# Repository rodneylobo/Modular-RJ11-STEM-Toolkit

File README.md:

# Modular-RJ11-STEM-Toolkit
This Toolkit prototype because of MIT's Thrifty MakerSpace project.
The prototype was tested in low income schools with enormous success in inducing the habit of 'Making' in kids.
The Modularity in the design makes the kit more affordable than existing kits.

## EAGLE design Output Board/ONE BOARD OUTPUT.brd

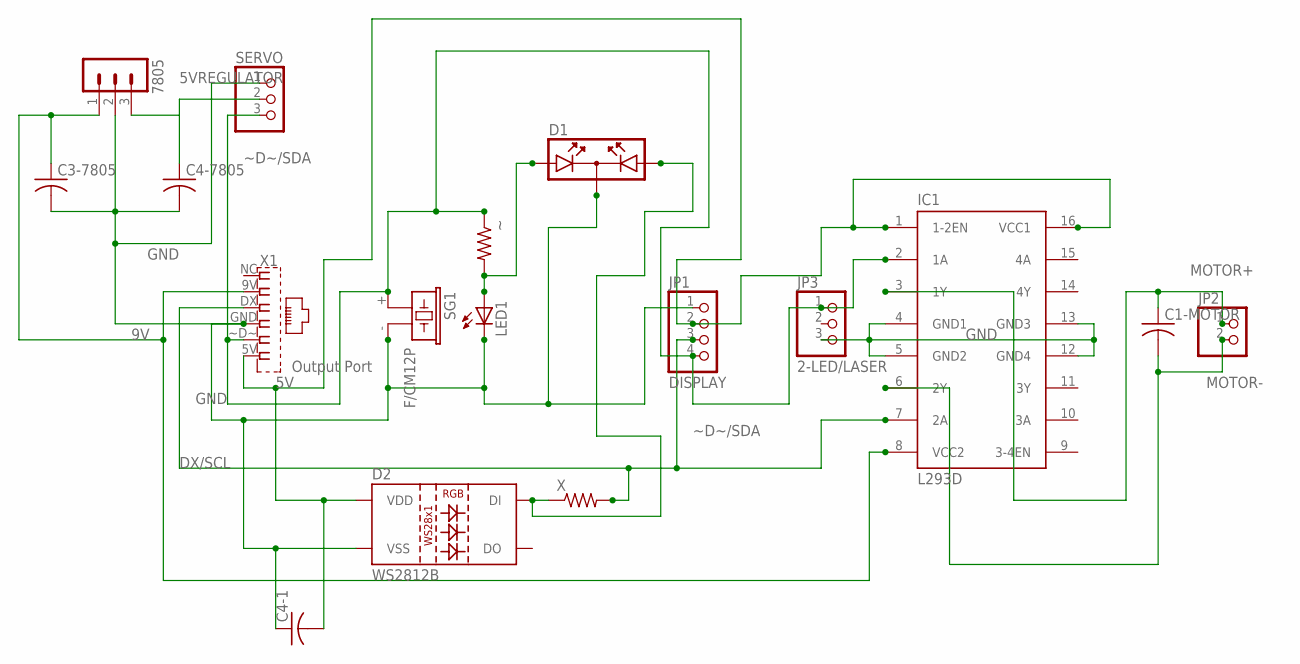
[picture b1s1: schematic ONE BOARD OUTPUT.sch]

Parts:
7805: MA03-1
C1-MOTOR, C3-7805, C4-1, C4-7805: C-US025-030X050; C025-030X050
D1: DUOLED
D2: WS2812B
IC1: L293D; DIL16
JP1: DISPLAY; 1X04
JP2: PINHD-1X2; 1X02
JP3: 2-LED/LASER; 1X03
LED1: LED10MM
SERVO: PINHD-1X3; 1X03
SG1: F/CM12P
X: R-US_0207/10; 0207/10
X1: Output Port; ELEMENTORY-OUT-SEN
~: R-US_0207/10; 0207/10

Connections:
5V: C4-1.2, D2.1 (VDD), IC1.1 (1-2EN), IC1.16 (VCC1), JP1.2, X1.5V (6)
5VREGULATOR: 7805.3, C4-7805.1, SERVO.2
9V: 7805.1, C3-7805.1, IC1.8 (VCC2), X1.9V (2)
DX/SCL: IC1.7 (2A), JP1.3, X.2, X1.DX (3)
GND: 7805.2, C3-7805.2, C4-1.1, C4-7805.2, D1.K, D2.3 (VSS), IC1.4 (GND1), IC1.5 (GND2), IC1.12 (GND4), IC1.13 (GND3), JP1.1, JP3.3, LED1.K (C), SERVO.1, SG1.- (2), X1.GND (4)
LED_SIG: D1.A1, LED1.A, ~.2
MOTOR+: C1-MOTOR.1, IC1.3 (1Y), JP2.1
MOTOR-: C1-MOTOR.2, IC1.6 (2Y), JP2.2
unnamed: D1.A2, D2.4 (DI), X.1
~D~/SDA: IC1.2 (1A), JP1.4, JP3.1, SERVO.3, SG1.+ (1), X1.~D~ (5), ~.1

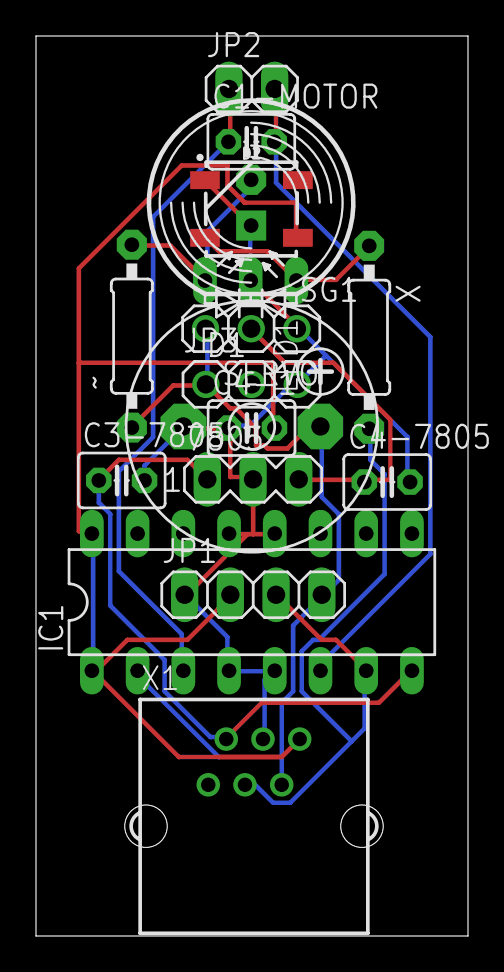
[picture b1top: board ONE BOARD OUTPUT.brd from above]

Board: 2 copper layers, 24.0 x 50.0 mm, 17 parts (0 on the bottom side), 10 nets.

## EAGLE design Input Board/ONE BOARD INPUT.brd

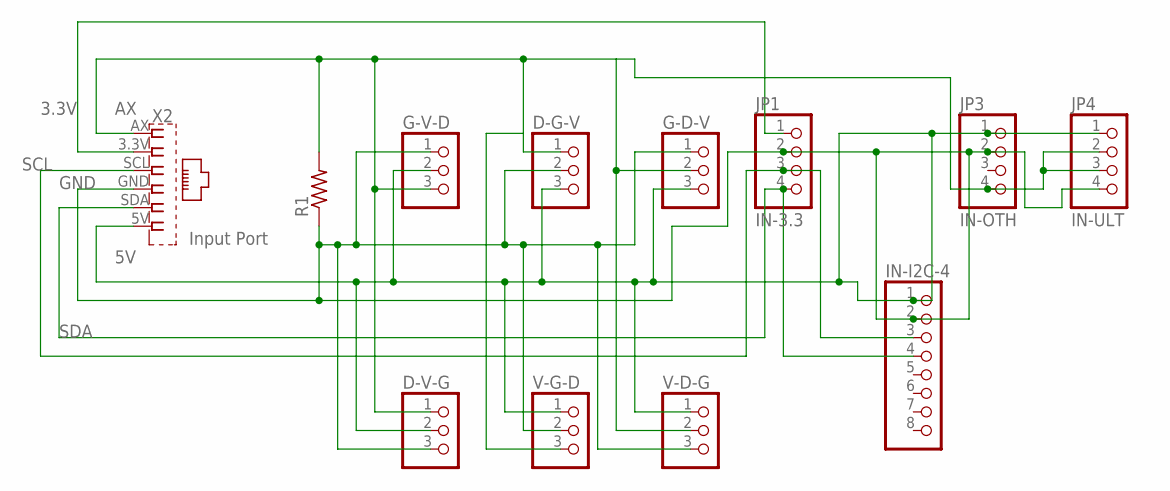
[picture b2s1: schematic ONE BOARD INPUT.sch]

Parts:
D-G-V: PINHD-1X3; 1X03
D-V-G: PINHD-1X3; 1X03
G-D-V: PINHD-1X3; 1X03
G-V-D: PINHD-1X3; 1X03
IN-I2C-4: PINHD-1X8; 1X08
JP1: IN-3.3; 1X04
JP3: IN-OTH; 1X04
JP4: IN-ULT; 1X04
R1: R-US_0207/10; 0207/10
V-D-G: PINHD-1X3; 1X03
V-G-D: PINHD-1X3; 1X03
X2: Input Port; ELEMENTORY-IN-SEN

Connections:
3.3V: JP1.1, X2.3.3V (2)
5V: D-G-V.3, D-V-G.2, G-D-V.3, G-V-D.2, IN-I2C-4.1, JP3.1, JP4.1, V-D-G.1, V-G-D.1, X2.5V (6)
AX: D-G-V.1, D-V-G.1, G-D-V.2, G-V-D.3, JP3.4, JP4.2, JP4.3, R1.2, V-D-G.2, V-G-D.3, X2.AX (1)
GND: D-G-V.2, D-V-G.3, G-D-V.1, G-V-D.1, IN-I2C-4.2, JP1.2, JP3.2, JP4.4, R1.1, V-D-G.3, V-G-D.2, X2.GND (4)
SCL: IN-I2C-4.3, JP1.3, X2.SCL (3)
SDA: IN-I2C-4.4, JP1.4, X2.SDA (5)

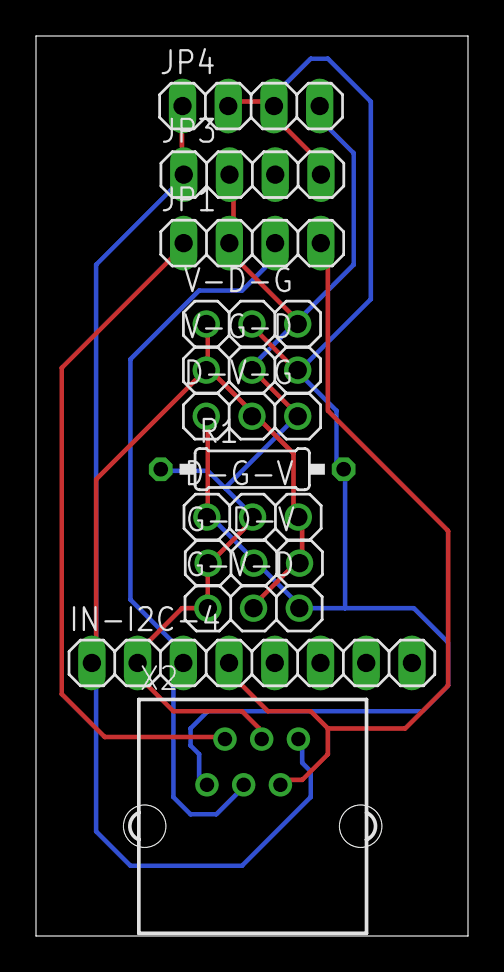
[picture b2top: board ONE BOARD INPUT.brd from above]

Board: 2 copper layers, 24.0 x 50.0 mm, 12 parts (0 on the bottom side), 6 nets.

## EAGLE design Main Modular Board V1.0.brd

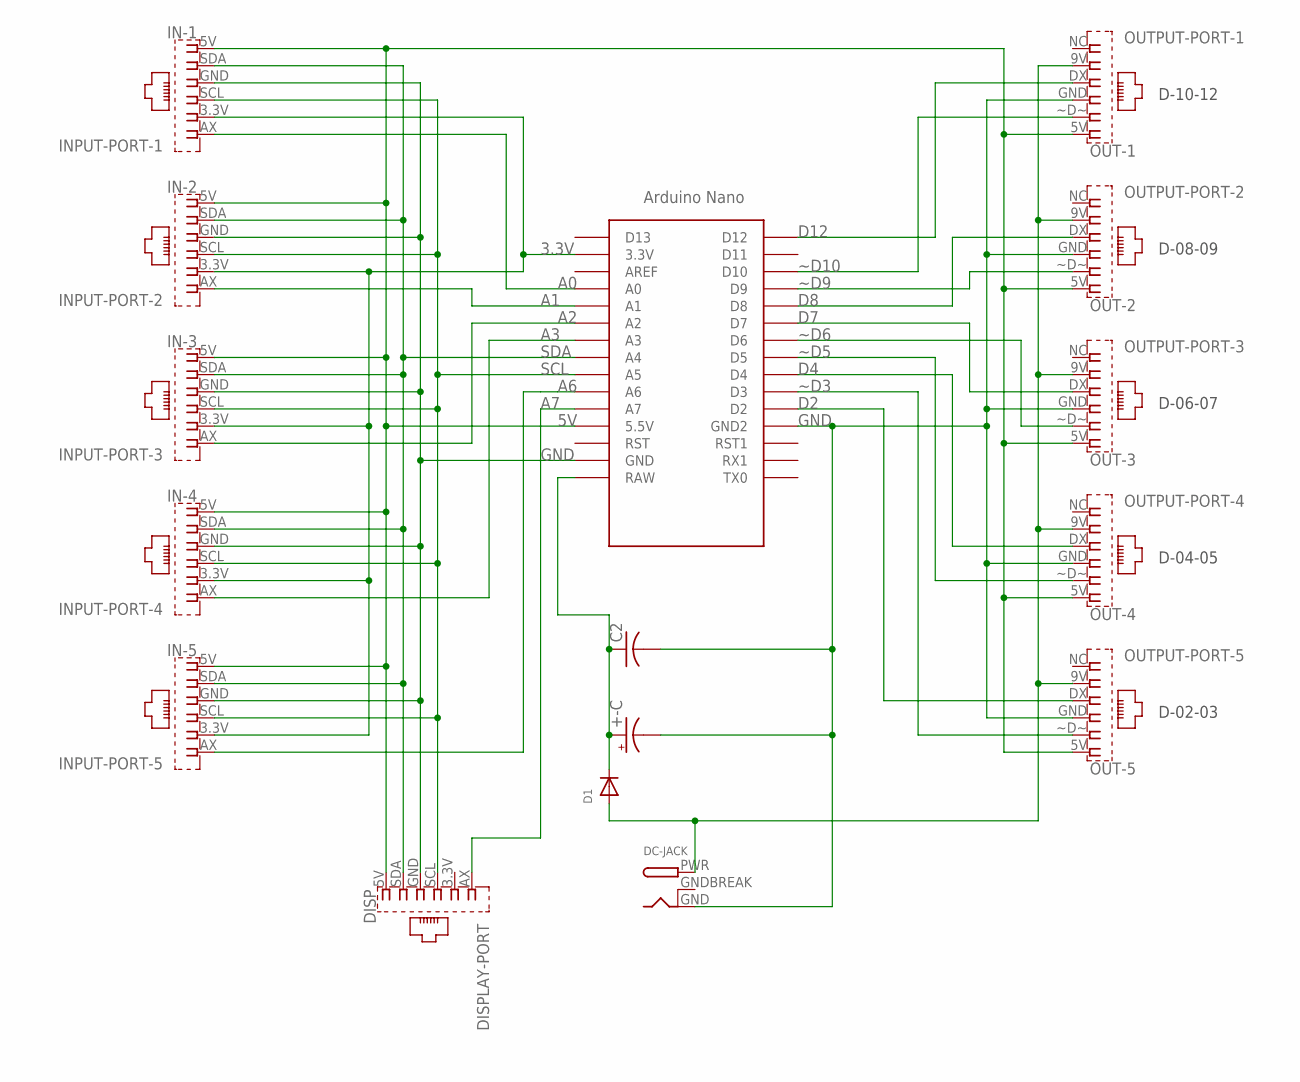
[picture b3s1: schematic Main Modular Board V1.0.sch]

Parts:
+-C: CPOL-USE2.5-6; E2,5-6
C2: C-US025-025X050; C025-025X050
D1: DIODEDO-1N4148; DO-1N4148
DC-JACK: DCBARRELPTH; DCJACK_2MM_PTH
DISP: DISPLAY-PORT; ELEMENTORY-IN-BRD
IN-1: INPUT-PORT-1; ELEMENTORY-IN-BRD
IN-2: INPUT-PORT-2; ELEMENTORY-IN-BRD
IN-3: INPUT-PORT-3; ELEMENTORY-IN-BRD
IN-4: INPUT-PORT-4; ELEMENTORY-IN-BRD
IN-5: INPUT-PORT-5; ELEMENTORY-IN-BRD
OUT-1: OUTPUT-PORT-1; ELEMENTORY-OUT-BRD
OUT-2: OUTPUT-PORT-2; ELEMENTORY-OUT-BRD
OUT-3: OUTPUT-PORT-3; ELEMENTORY-OUT-BRD
OUT-4: OUTPUT-PORT-4; ELEMENTORY-OUT-BRD
OUT-5: OUTPUT-PORT-5; ELEMENTORY-OUT-BRD
U$1: NANO

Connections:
3.3V: IN-1.3.3V (5), IN-2.3.3V (5), IN-3.3.3V (5), IN-4.3.3V (5), IN-5.3.3V (5), U$1.3.3V
5V: DISP.5V (1), IN-1.5V (1), IN-2.5V (1), IN-3.5V (1), IN-4.5V (1), IN-5.5V (1), OUT-1.5V (1), OUT-2.5V (1), OUT-3.5V (1), OUT-4.5V (1), OUT-5.5V (1), U$1.5V (5.5V)
9V: D1.A, DC-JACK.PWR, OUT-1.9V (5), OUT-2.9V (5), OUT-3.9V (5), OUT-4.9V (5), OUT-5.9V (5)
A0: IN-1.AX (6), U$1.A0
A1: IN-2.AX (6), U$1.A1
A2: IN-3.AX (6), U$1.A2
A3: IN-4.AX (6), U$1.A3
A6: IN-5.AX (6), U$1.A6
A7: DISP.AX (6), U$1.A7
D2: OUT-5.DX (4), U$1.D2
D4: OUT-4.DX (4), U$1.D4
D7: OUT-3.DX (4), U$1.D7
D8: OUT-2.DX (4), U$1.D8
D12: OUT-1.DX (4), U$1.D12
GND: +-C.-, C2.2, DC-JACK.GND, DISP.GND (3), IN-1.GND (3), IN-2.GND (3), IN-3.GND (3), IN-4.GND (3), IN-5.GND (3), OUT-1.GND (3), OUT-2.GND (3), OUT-3.GND (3), OUT-4.GND (3), OUT-5.GND (3), U$1.GND, U$1.GND1 (GND2)
GNDBREAK: DC-JACK.GNDBREAK
unnamed: +-C.+, C2.1, D1.C, U$1.RAW
SCL: DISP.SCL (4), IN-1.SCL (4), IN-2.SCL (4), IN-3.SCL (4), IN-4.SCL (4), IN-5.SCL (4), U$1.A5
SDA: DISP.SDA (2), IN-1.SDA (2), IN-2.SDA (2), IN-3.SDA (2), IN-4.SDA (2), IN-5.SDA (2), U$1.A4
~D3: OUT-5.~D~ (2), U$1.D3
~D5: OUT-4.~D~ (2), U$1.D5
~D6: OUT-3.~D~ (2), U$1.D6
~D9: OUT-2.~D~ (2), U$1.D9
~D10: OUT-1.~D~ (2), U$1.D10

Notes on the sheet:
D-02-03
D-04-05
D-06-07
D-08-09
D-10-12

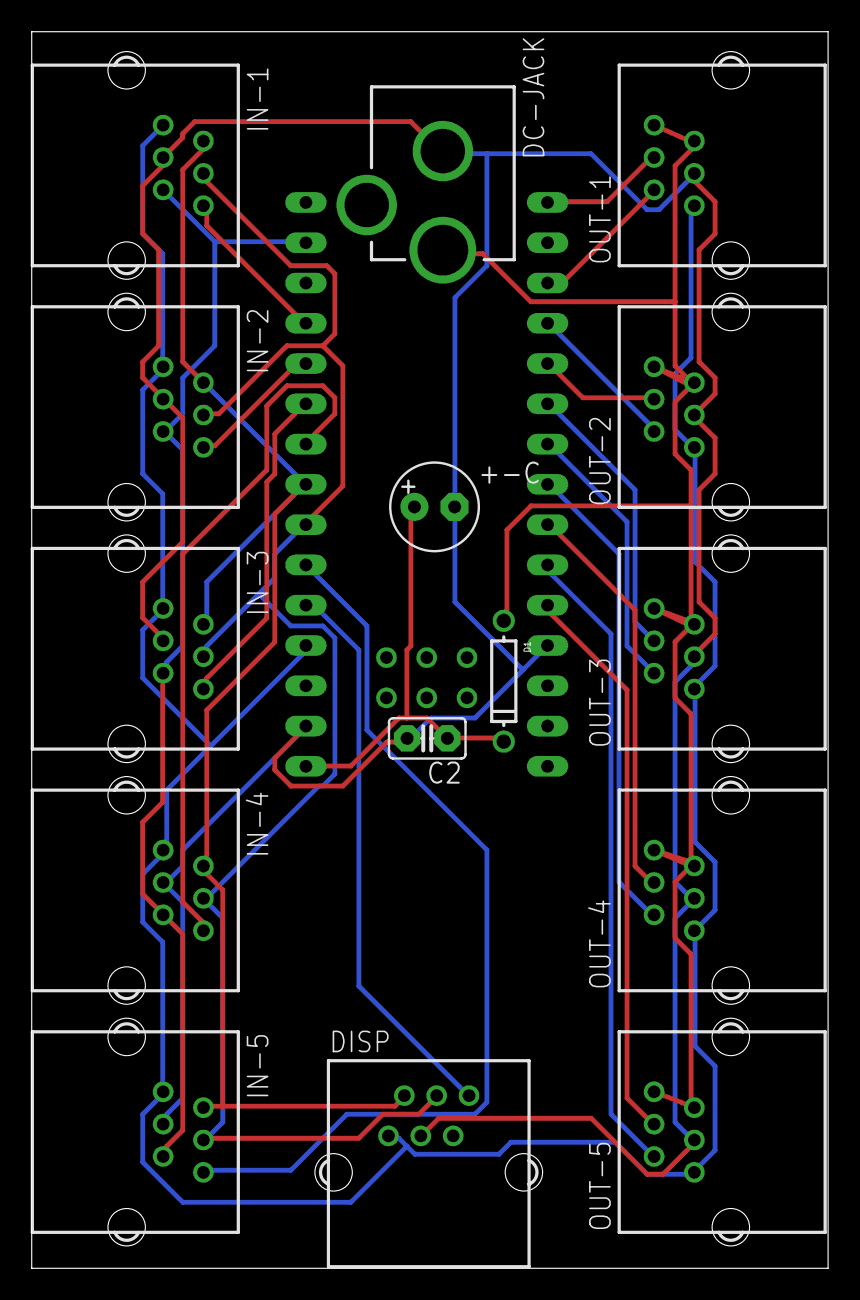
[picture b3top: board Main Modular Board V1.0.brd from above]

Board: 2 copper layers, 50.2 x 78.0 mm, 16 parts (0 on the bottom side), 23 nets.

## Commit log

2018-10-02 Set theme jekyll-theme-slate
2018-10-02 Add files via upload
    Main Board Eagle Files added
2018-10-02 Add files via upload
    Renamed files and added the eagle library used
2018-10-05 Create Input One Board
2018-10-05 Add files via upload
    Input Board for Moduler RJ11 STEM Toolkit
2018-10-05 Create One Output Board
2018-10-05 Add files via upload
    One Output Board for Modular RJ11 STEM Toolkit
2018-10-05 Create Library Readme
2018-10-05 Rename One Output Board to One Output Board Readme
2018-10-05 Rename Input One Board to Input One Board Readme
2018-10-05 Create Main Board Readme
2018-10-05 Update Main Board Readme
2018-10-05 Create README.md
    Created folders, added a new readme, made the entire things look more presentable

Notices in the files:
parts and their libraries:
SparkFun-LED: Licensing: Creative Commons ShareAlike 4.0 International - https://creativecommons.org/licenses/by-sa/4.0
